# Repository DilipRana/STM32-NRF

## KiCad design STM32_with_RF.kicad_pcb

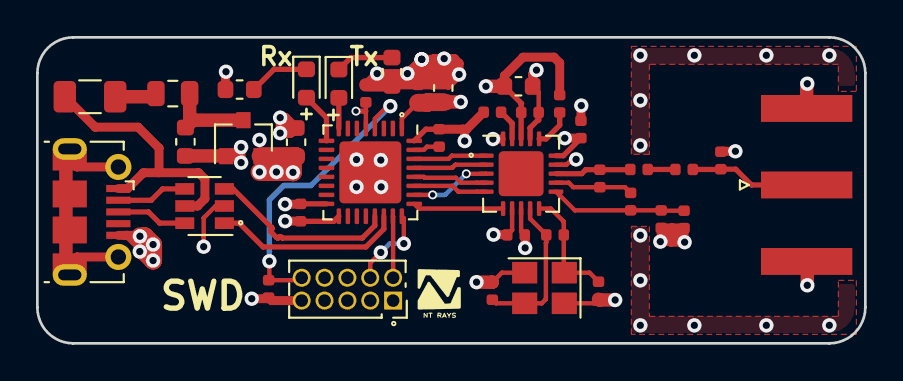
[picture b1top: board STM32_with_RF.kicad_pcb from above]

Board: 4 copper layers, 46.0 x 17.0 mm, 38 parts (0 on the bottom side), 32 nets.

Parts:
C1, C2: 100u; C_0603_1608Metric
C3: 1u; C_0603_1608Metric
C4, C5, C6, C15: 100n; C_0402_1005Metric
C7: 1p5; C_0402_1005Metric
C8: 1p; C_0402_1005Metric
C9: 2n2; C_0402_1005Metric
C10: 4p7; C_0402_1005Metric
C11: 10u; C_0603_1608Metric
C12, C13, C14: 10n; C_0402_1005Metric
C16, C17: 12p; C_0402_1005Metric
C18: 33n; C_0402_1005Metric
D1: GR; LED_0603_1608Metric
D2: YE; LED_0603_1608Metric
F1: 100mA; Fuse_1206_3216Metric
FB1: 100 @ 100MHz; L_0805_2012Metric
J1: USB_B_Micro; USB_Micro-B_Molex-105017-0001
J2: SMA Connector; SMA_Amphenol_132289_EdgeMount
J3: ARM 10 Pin; PinSocket_2x05_P1.27mm_Vertical
L1: 3n9; L_0402_1005Metric
L2: 8n2; L_0402_1005Metric
L3: 2n7; L_0402_1005Metric
R1: 10k; R_0402_1005Metric
R2, R3: 2k2; R_0603_1608Metric
R4: 1M; R_0402_1005Metric
R5: 22k; R_0402_1005Metric
U1: XC6206P332MR; SOT-23
U2: USBLC6-2SC6; SOT-23-6
U3: STM32L432KBU6; QFN-32-1EP_5x5mm_P0.5mm_EP3.45x3.45mm
U4: nRF24L01P; QFN-20-1EP_4x4mm_P0.5mm_EP2.5x2.5mm
Y1: 16MHz; Crystal_SMD_3225-4Pin_3.2x2.5mm

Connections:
+3V3: C2.1, C3.1, C4.1, C5.1, C6.1, C11.1, C12.1, C13.1, C14.1, J3.1, R5.1, U1.2, U3.1, U3.5, U3.17, U4.7, U4.15, U4.18
+5V: F1.1, J1.1, U2.5
GND: C1.2, C2.2, C3.2, C4.2, C5.2, C6.2, C8.1, C9.1, C10.1, C11.2, C12.2, C13.2, C14.2, C15.2, C16.1, C17.1, C18.2, J1.5, J2.2, J3.3, J3.5, J3.9, R1.2, R2.2, R3.2, U1.1, U2.2, U3.16, U3.32, U3.33, U4.8, U4.14, U4.17, U4.20, Y1.2, Y1.4
NRF_ANT1: L2.2, L3.1, U4.12
NRF_ANT2: L1.1, L2.1, U4.13
NRF_CE: U3.30, U4.1
NRF_IRQ: U3.25, U4.6
NRF_VDD_PA: C9.2, C10.2, L3.2, U4.11
NRF_XC1: C16.2, R4.2, U4.10, Y1.1
NRF_XC2: C17.2, R4.1, U4.9, Y1.3
NRST: C15.1, J3.10, U3.4
unnamed: C1.1, FB1.1, U1.3
unnamed: C7.1, C8.2, J2.1
unnamed: C7.2, L1.2
unnamed: C18.1, U4.19
unnamed: D1.1, R2.1
unnamed: D1.2, U3.9
unnamed: D2.1, R3.1
unnamed: D2.2, U3.8
unnamed: F1.2, FB1.2
unnamed: R1.1, U3.31
unnamed: R5.2, U4.16
SPI3_ICS: U3.29, U4.2
SPI3_MISO: U3.27, U4.5
SPI3_MOSI: U3.28, U4.4
SPI3_SCK: U3.26, U4.3
SWCLK: J3.4, U3.24
SWDIO: J3.2, U3.23
USB_CONN_D+: J1.3, U2.6
USB_CONN_D-: J1.2, U2.4
USB_D+: U2.1, U3.22
USB_D-: U2.3, U3.21

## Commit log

2023-05-27 Complete Design
